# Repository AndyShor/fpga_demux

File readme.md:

# FPGA implementation of ADG732  32 chanel DEMUX chip control

FPGA testing of verilog code to control ADG732  32 chanel DEMUX chip.
Assumed FPGA is iCESugar-nano, according to documentation https://github.com/wuxx/icesugar-nano
ice40 FPGA is LP1K and package type is CM36.

requires installed icestorm toolchain: yosys, nextpnr, iceprog.
For simulations requires iverilog, GTKwave. iCESugar-nano is supported by apio.
This version is for testing with a PMOD LED unit visualizing output channels.
LED unit uses common anode and logic signals must be inverted, which is done by pmod_inverter.v module.

in order to simulate

`$ make sim`

simulation has clock division of 100 instead of 10M for covenience. Clock division is to the demux module as a parameter on instantiation.

in order to synthesise bitstream for a demo with inverting LED PMOD unit

`$ make build_pmod `

on the photo red wire sets rst to low, LEDs D7-D3 show value at 5-bit channel selection bus, D7 lowest bit D3 highest.

Switching signal test. Signals measured with scope yellow trace - CS is set high prior to changing green trace WR L-> H,
that triggers actual switch.

in order to synthesise bitstream for controlling real demux chip

`$ make build_demux `

When connected to actual ADG732BSUZ on a break out board - performs switching as expected at 10 MHZ FPGA clock frequency.

Design files for the break out board are contained in the PCB folder including KiCAD project and gerber files.

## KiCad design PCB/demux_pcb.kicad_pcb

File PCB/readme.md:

This folder contains information about the PCB design necessary to reproduce the breakout board.
the controls  are connected to J3 pin array, pin arrays J1, J2, J4 contain outputs and the single input is located 
in the middle of J2

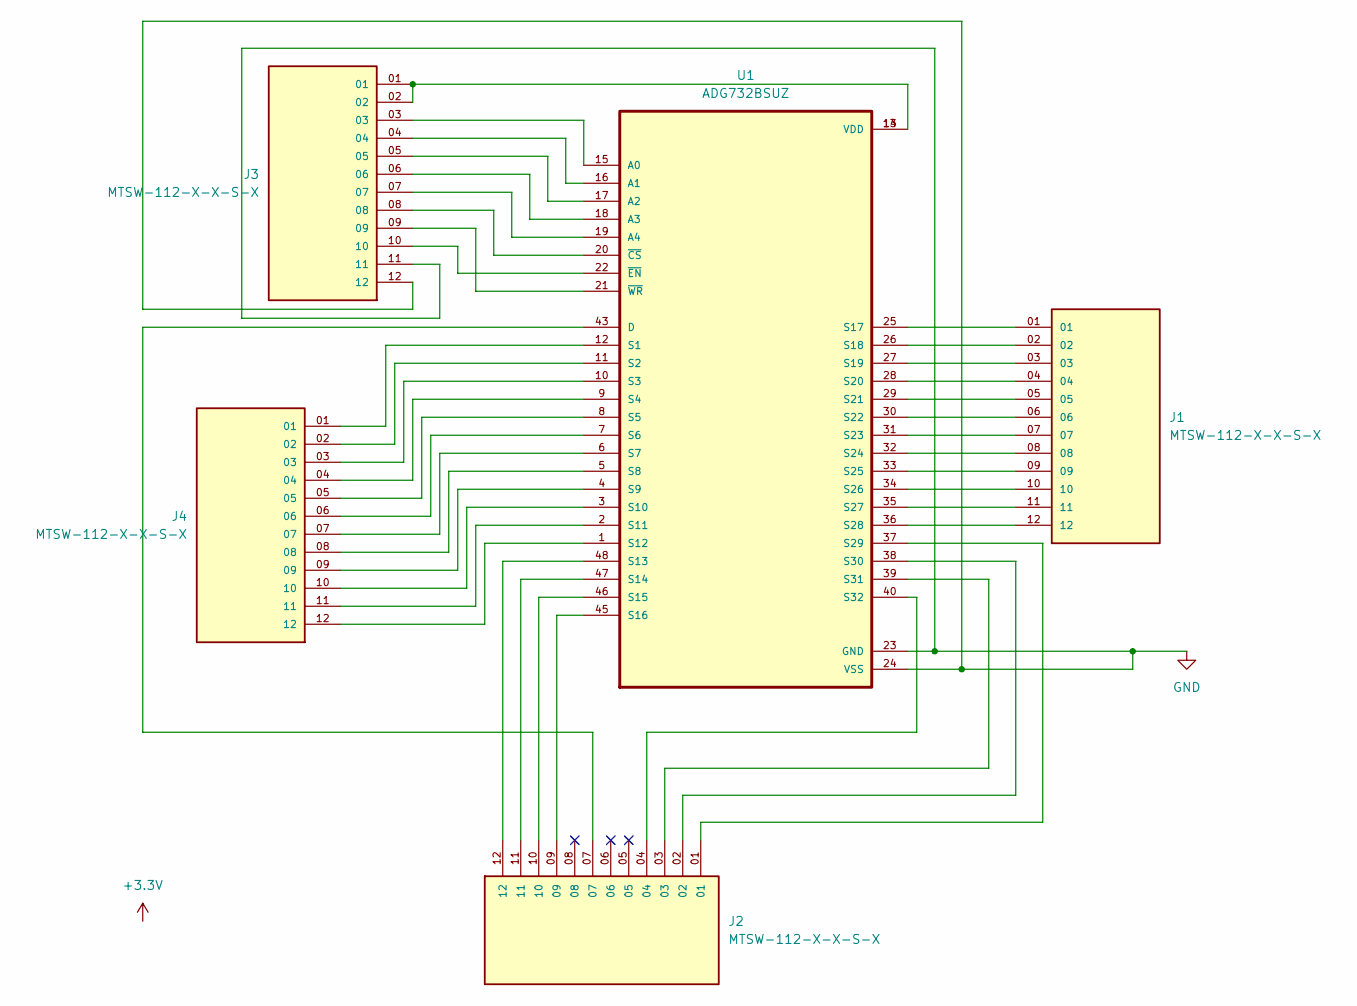
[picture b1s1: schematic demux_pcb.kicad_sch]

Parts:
J1, J2, J3, J4: MTSW-112-X-X-S-X; SAMTEC_MTSW-112-X-X-S-X; PARTREV A
U1: ADG732BSUZ; QFP50P900X900X120-49N

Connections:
GND: J3.11, J3.12, U1.23 (GND), U1.24 (VSS)
unnamed: J3.01, J3.02, U1.13 (VDD), U1.14 (VDD)
unnamed: J3.03, U1.15 (A0)
unnamed: J3.04, U1.16 (A1)
unnamed: J3.05, U1.17 (A2)
unnamed: J3.06, U1.18 (A3)
unnamed: J3.07, U1.19 (A4)
unnamed: J2.07, U1.43 (D)
unnamed: J4.01, U1.12 (S1)
unnamed: J4.02, U1.11 (S2)
unnamed: J4.03, U1.10 (S3)
unnamed: J4.04, U1.9 (S4)
unnamed: J4.05, U1.8 (S5)
unnamed: J4.06, U1.7 (S6)
unnamed: J4.07, U1.6 (S7)
unnamed: J4.08, U1.5 (S8)
unnamed: J4.09, U1.4 (S9)
unnamed: J4.10, U1.3 (S10)
unnamed: J4.11, U1.2 (S11)
unnamed: J4.12, U1.1 (S12)
unnamed: J2.12, U1.48 (S13)
unnamed: J2.11, U1.47 (S14)
unnamed: J2.10, U1.46 (S15)
unnamed: J2.09, U1.45 (S16)
unnamed: J1.01, U1.25 (S17)
unnamed: J1.02, U1.26 (S18)
unnamed: J1.03, U1.27 (S19)
unnamed: J1.04, U1.28 (S20)
unnamed: J1.05, U1.29 (S21)
unnamed: J1.06, U1.30 (S22)
unnamed: J1.07, U1.31 (S23)
unnamed: J1.08, U1.32 (S24)
unnamed: J1.09, U1.33 (S25)
unnamed: J1.10, U1.34 (S26)
unnamed: J1.11, U1.35 (S27)
unnamed: J1.12, U1.36 (S28)
unnamed: J2.01, U1.37 (S29)
unnamed: J2.02, U1.38 (S30)
unnamed: J2.03, U1.39 (S31)
unnamed: J2.04, U1.40 (S32)
unnamed: J3.08, U1.20 (~CS)
unnamed: J3.10, U1.22 (~EN)
unnamed: J3.09, U1.21 (~WR)

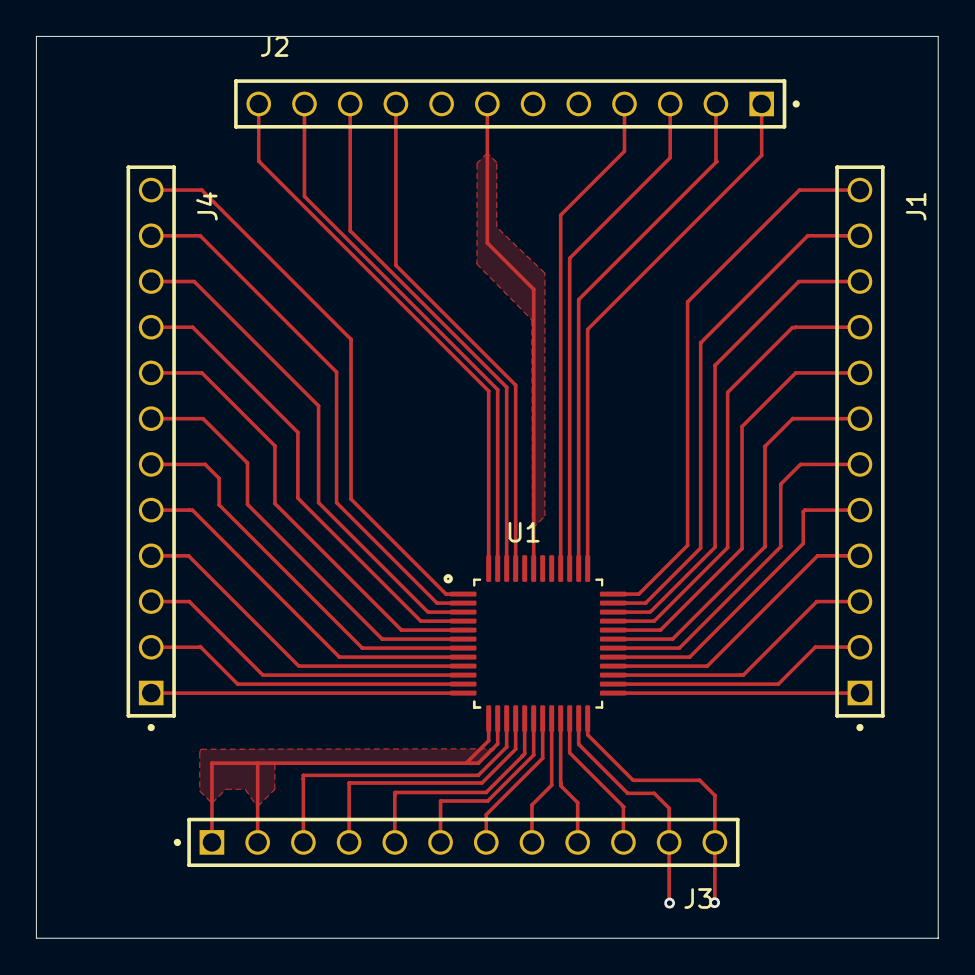
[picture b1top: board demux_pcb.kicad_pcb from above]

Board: 2 copper layers, 50.1 x 50.1 mm, 5 parts (0 on the bottom side), 43 nets.

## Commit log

2025-07-03 Created readme.md
2025-07-03 added files
2025-07-03 Update Makefile
2025-07-06 Update io.pcf
    inverted names for PMOD module
2025-07-06 Update Makefile
    changed makefile for pmod inverter
2025-08-18 added demux test pics
2025-09-06 modified makefile for separate build of PMOD inverting demo and normal use
2025-09-06 added sythesysed files
2025-09-07 tested on Hardware before push
2025-09-09 Update demux.v
    synchronized with demux used for ASIC as blocking and non-blocking assignments mixed are an issue in there.
2025-09-10 Create readme.md for PCB part
2025-09-10 added basic PCB files
2025-09-10 added production files
2025-09-10 added ADG732 footprint
2025-09-17 Create LICENSE

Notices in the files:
readme.md:
License: MIT
